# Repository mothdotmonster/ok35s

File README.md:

# OK35s

[click here if you want to get one premade](https://mothdotmonster-shop.square.site/product/ok35s/11)

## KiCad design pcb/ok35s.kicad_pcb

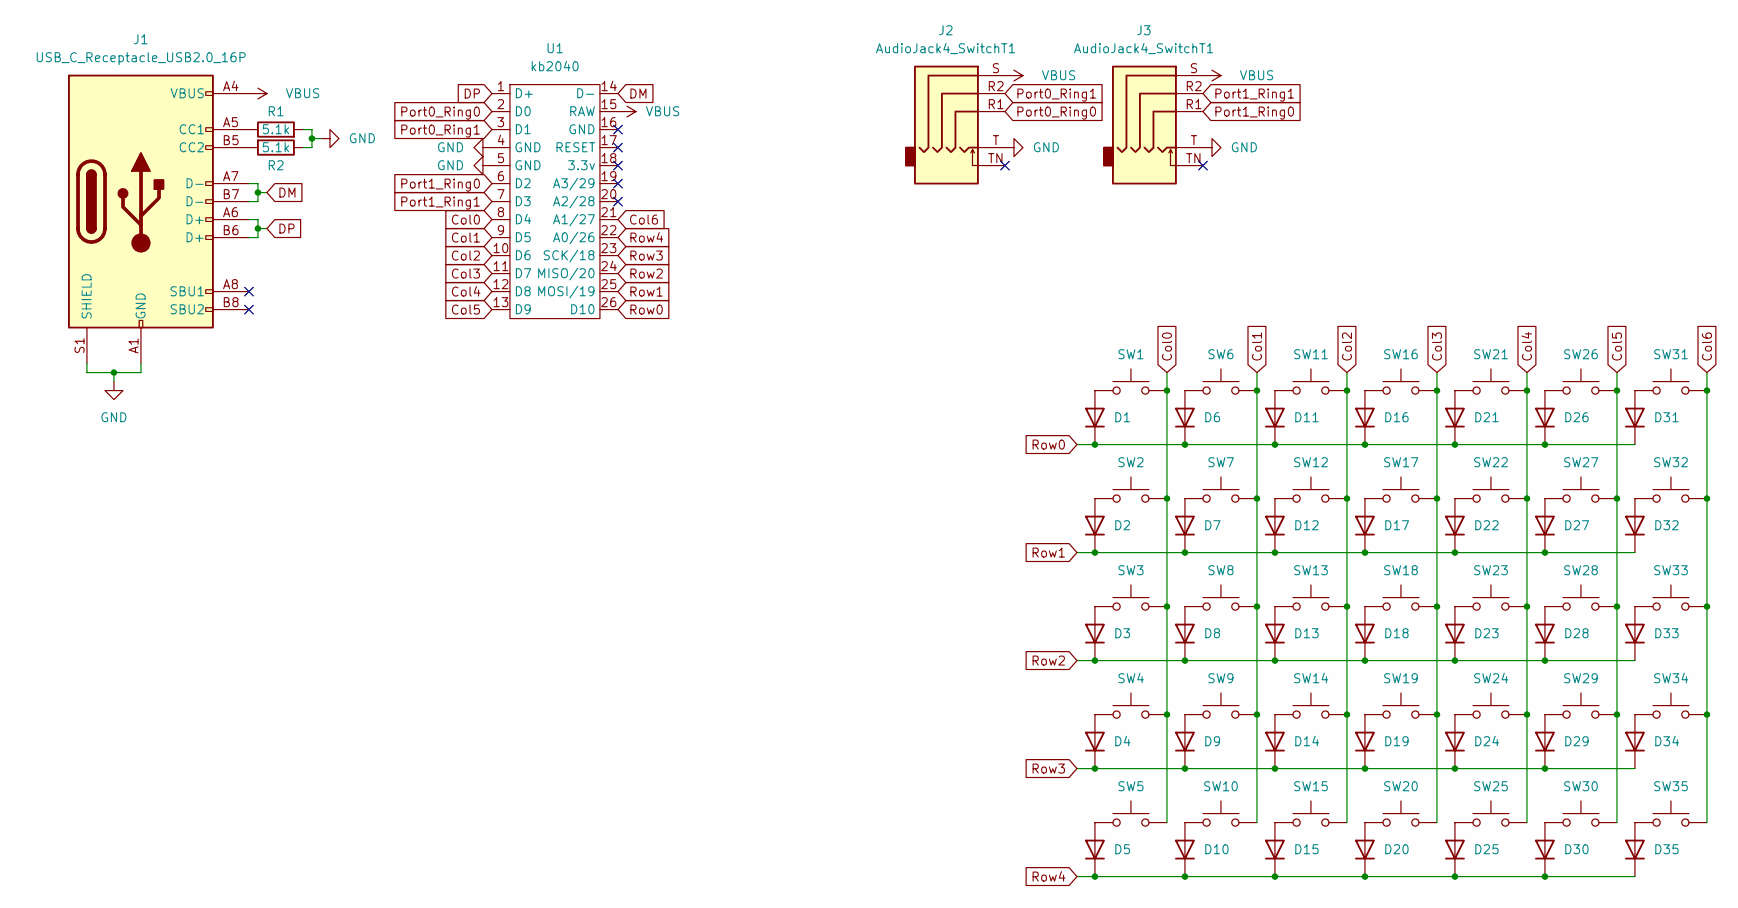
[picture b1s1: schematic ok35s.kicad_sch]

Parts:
D1, D2, D3, D4, D5, D6, D7, D8, D9, D10, D11, D12, D13, D14, D15, D16, D17, D18, D19, D20, D21, D22, D23, D24, D25, D26, D27, D28, D29, D30, D31, D32, D33, D34, D35: D; D_SOD-323; JLC C2128
J1: USB_C_Receptacle_USB2.0_16P; USB_C_Receptacle_HRO_TYPE-C-31-M-12; JLC C165948
J2, J3: AudioJack4_SwitchT1; Jack_3.5mm_PJ320D_Horizontal; JLC C431535
R1, R2: 5.1k; R_0603_1608Metric; JLC C23186
SW1, SW2, SW3, SW4, SW5, SW6, SW7, SW8, SW9, SW10, SW11, SW12, SW13, SW14, SW15, SW16, SW17, SW18, SW19, SW20, SW21, SW22, SW23, SW24, SW25, SW26, SW27, SW28, SW29, SW30, SW31, SW32, SW33, SW34, SW35: SW_Push; SW_Hotswap_Kailh_MX_1.00u; JLC C41430893
U1: kb2040

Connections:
Col0: SW1.2, SW2.2, SW3.2, SW4.2, SW5.2, U1.8 (D4)
Col1: SW6.2, SW7.2, SW8.2, SW9.2, SW10.2, U1.9 (D5)
Col2: SW11.2, SW12.2, SW13.2, SW14.2, SW15.2, U1.10 (D6)
Col3: SW16.2, SW17.2, SW18.2, SW19.2, SW20.2, U1.11 (D7)
Col4: SW21.2, SW22.2, SW23.2, SW24.2, SW25.2, U1.12 (D8)
Col5: SW26.2, SW27.2, SW28.2, SW29.2, SW30.2, U1.13 (D9)
Col6: SW31.2, SW32.2, SW33.2, SW34.2, SW35.2, U1.21 (A1/27)
DM: J1.A7 (D-), J1.B7 (D-), U1.14 (D-)
DP: J1.A6 (D+), J1.B6 (D+), U1.1 (D+)
GND: J1.A1 (GND), J1.A12 (GND), J1.B1 (GND), J1.B12 (GND), J1.S1 (SHIELD), J2.T, J3.T, R1.2, R2.1, U1.4 (GND), U1.5 (GND)
unnamed: D1.2 (A), SW1.1
unnamed: D2.2 (A), SW2.1
unnamed: D3.2 (A), SW3.1
unnamed: D4.2 (A), SW4.1
unnamed: D5.2 (A), SW5.1
unnamed: D6.2 (A), SW6.1
unnamed: D7.2 (A), SW7.1
unnamed: D8.2 (A), SW8.1
unnamed: D9.2 (A), SW9.1
unnamed: D10.2 (A), SW10.1
unnamed: D11.2 (A), SW11.1
unnamed: D12.2 (A), SW12.1
unnamed: D13.2 (A), SW13.1
unnamed: D14.2 (A), SW14.1
unnamed: D15.2 (A), SW15.1
unnamed: D16.2 (A), SW16.1
unnamed: D17.2 (A), SW17.1
unnamed: D18.2 (A), SW18.1
unnamed: D19.2 (A), SW19.1
unnamed: D20.2 (A), SW20.1
unnamed: D21.2 (A), SW21.1
unnamed: D22.2 (A), SW22.1
unnamed: D23.2 (A), SW23.1
unnamed: D24.2 (A), SW24.1
unnamed: D25.2 (A), SW25.1
unnamed: D26.2 (A), SW26.1
unnamed: D27.2 (A), SW27.1
unnamed: D28.2 (A), SW28.1
unnamed: D29.2 (A), SW29.1
unnamed: D30.2 (A), SW30.1
unnamed: D31.2 (A), SW31.1
unnamed: D32.2 (A), SW32.1
unnamed: D33.2 (A), SW33.1
unnamed: D34.2 (A), SW34.1
unnamed: D35.2 (A), SW35.1
unnamed: J1.A5 (CC1), R1.1
unnamed: J1.B5 (CC2), R2.2
Port0_Ring0: J2.R1, U1.2 (D0)
Port0_Ring1: J2.R2, U1.3 (D1)
Port1_Ring0: J3.R1, U1.6 (D2)
Port1_Ring1: J3.R2, U1.7 (D3)
Row0: D1.1 (K), D6.1 (K), D11.1 (K), D16.1 (K), D21.1 (K), D26.1 (K), D31.1 (K), U1.26 (D10)
Row1: D2.1 (K), D7.1 (K), D12.1 (K), D17.1 (K), D22.1 (K), D27.1 (K), D32.1 (K), U1.25 (MOSI/19)
Row2: D3.1 (K), D8.1 (K), D13.1 (K), D18.1 (K), D23.1 (K), D28.1 (K), D33.1 (K), U1.24 (MISO/20)
Row3: D4.1 (K), D9.1 (K), D14.1 (K), D19.1 (K), D24.1 (K), D29.1 (K), D34.1 (K), U1.23 (SCK/18)
Row4: D5.1 (K), D10.1 (K), D15.1 (K), D20.1 (K), D25.1 (K), D30.1 (K), D35.1 (K), U1.22 (A0/26)
VBUS: J1.A4 (VBUS), J1.A9 (VBUS), J1.B4 (VBUS), J1.B9 (VBUS), J2.S, J3.S, U1.15 (RAW)

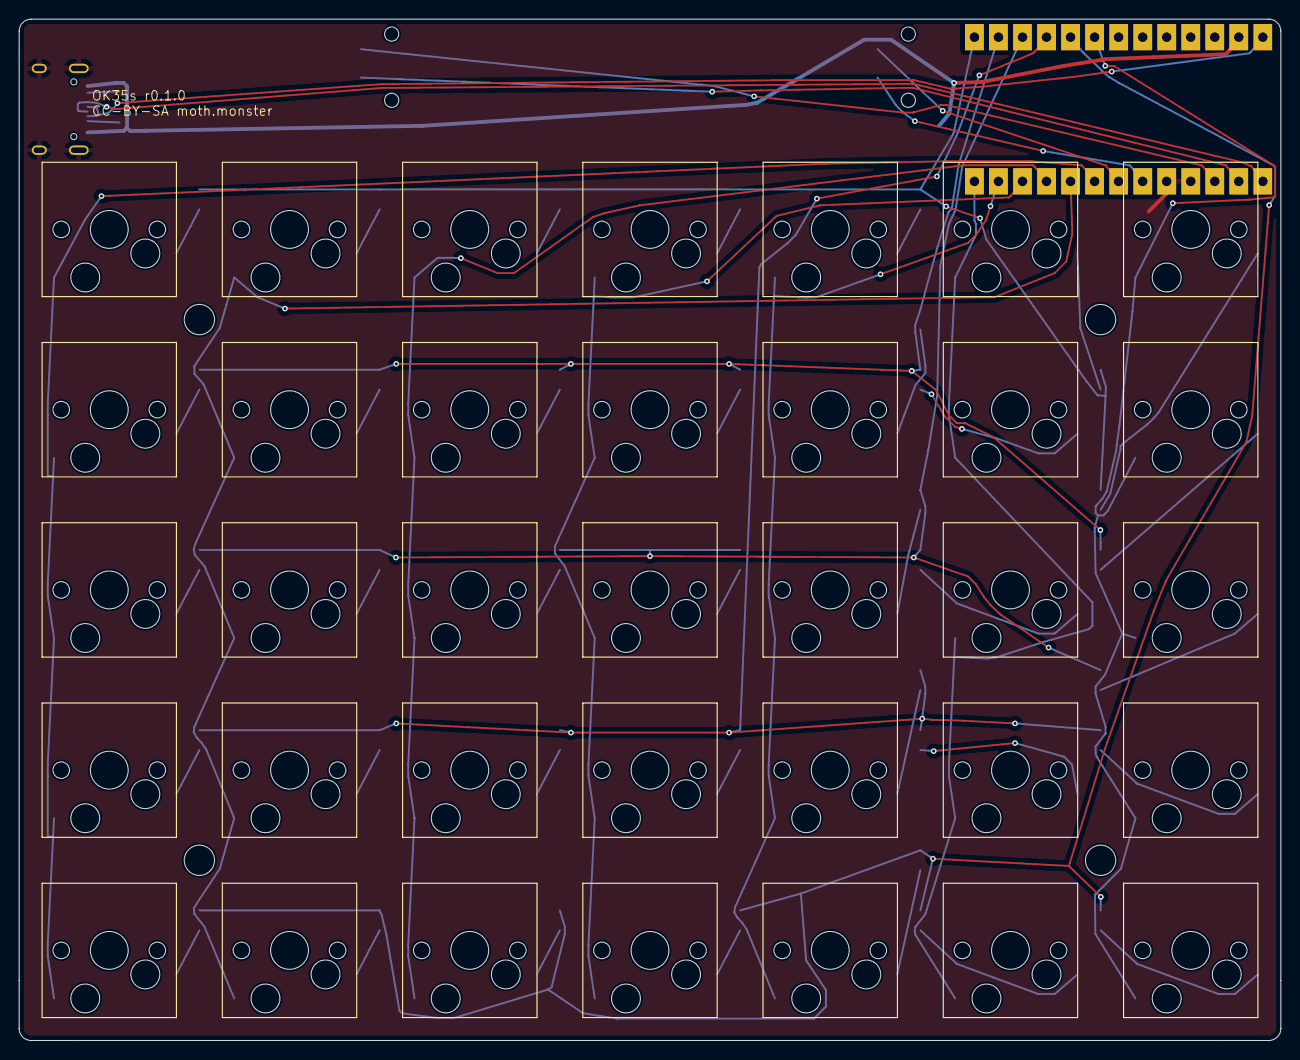
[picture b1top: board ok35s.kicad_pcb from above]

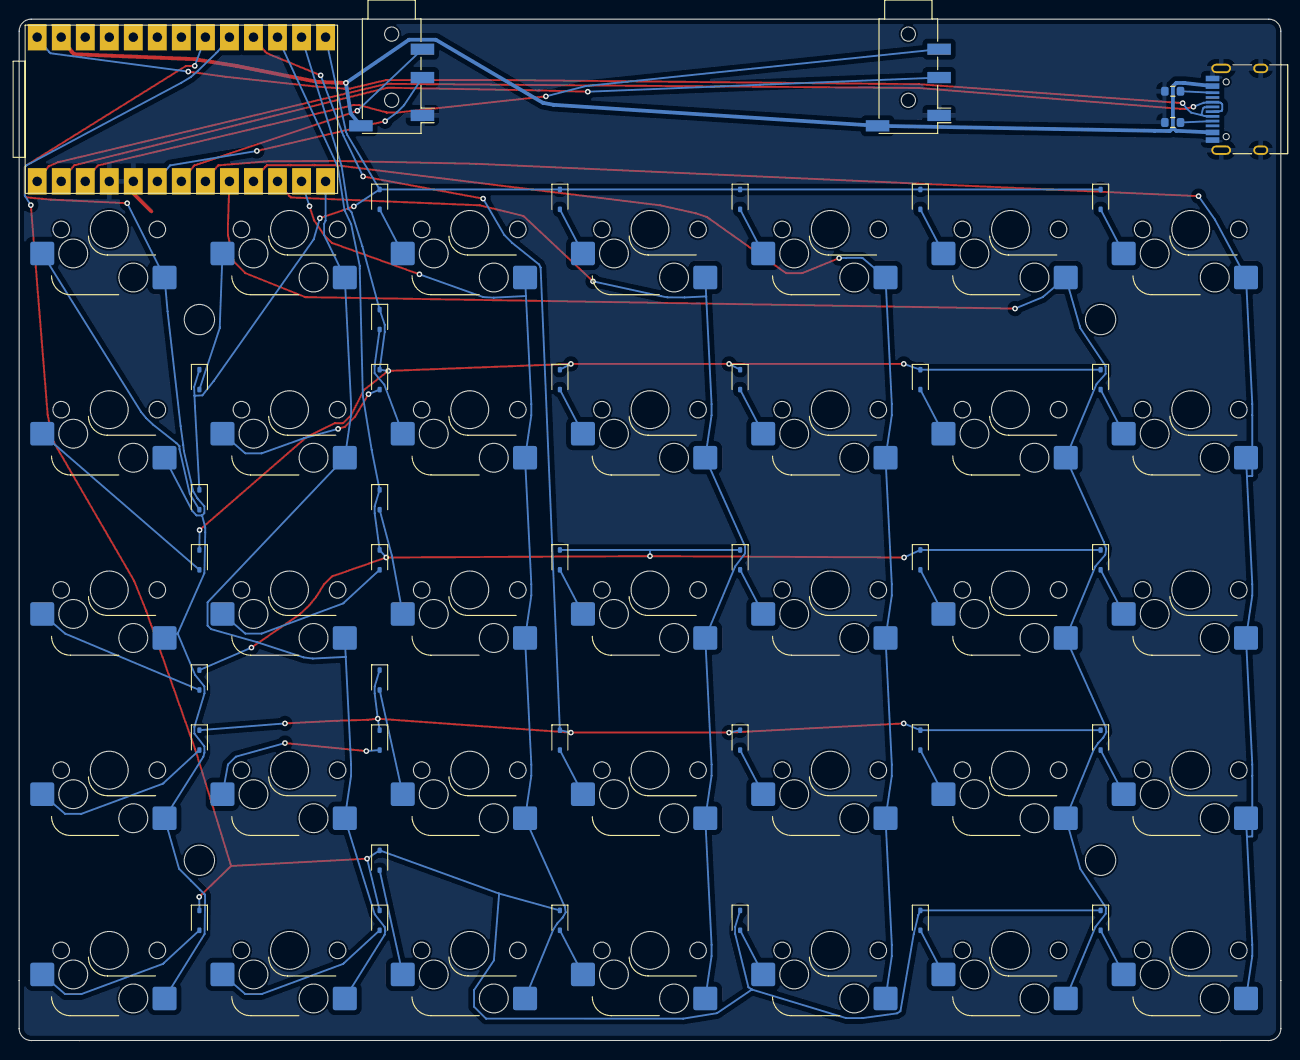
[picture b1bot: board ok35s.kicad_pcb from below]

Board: 2 copper layers, 133.4 x 108.0 mm, 80 parts (76 on the bottom side), 57 nets.

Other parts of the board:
HOLE1, HOLE2, HOLE3, HOLE4: MountingHole_3.2mm_M3_DIN965

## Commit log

2025-02-20 add license
2025-02-20 add case STLs
2025-02-20 upload firmware
2025-02-20 r0.1.0

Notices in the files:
pcb/ok35s.kicad_pcb:
CC-BY-SA moth.monster
